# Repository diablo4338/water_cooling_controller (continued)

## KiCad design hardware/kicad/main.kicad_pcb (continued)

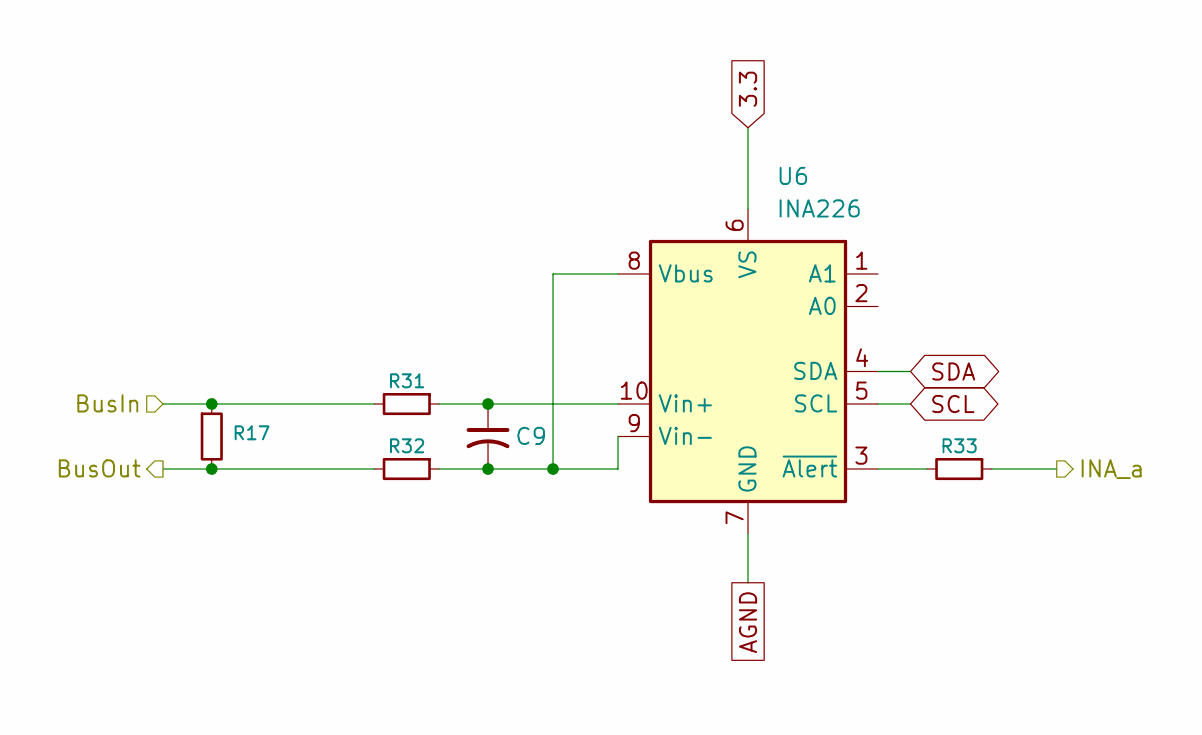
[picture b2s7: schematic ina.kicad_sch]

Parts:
C9: 0.1; C_0805_2012Metric_Pad1.18x1.45mm_HandSolder
R17: WSL2512R0470FEA; R_2512_6332Metric_Pad1.40x3.35mm_HandSolder
R31, R32: 10; R_0805_2012Metric_Pad1.20x1.40mm_HandSolder
R33: 1k; R_0805_2012Metric_Pad1.20x1.40mm_HandSolder
U6: INA226; VSSOP-10_3x3mm_P0.5mm

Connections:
3.3: U6.6 (VS); also elsewhere on the board
/esp/INA_a: R33.1; also elsewhere on the board
/fans/INA/BusIn: R17.1, R31.2; also elsewhere on the board
/fans/INA/BusOut: R17.2, R32.2; also elsewhere on the board
AGND: U6.7 (GND); also elsewhere on the board
unnamed: C9.2, R32.1, U6.8 (Vbus), U6.9 (Vin-)
unnamed: C9.1, R31.1, U6.10 (Vin+)
unnamed: R33.2, U6.3 (~Alert)
SCL: U6.5 (SCL); also elsewhere on the board
SDA: U6.4 (SDA); also elsewhere on the board

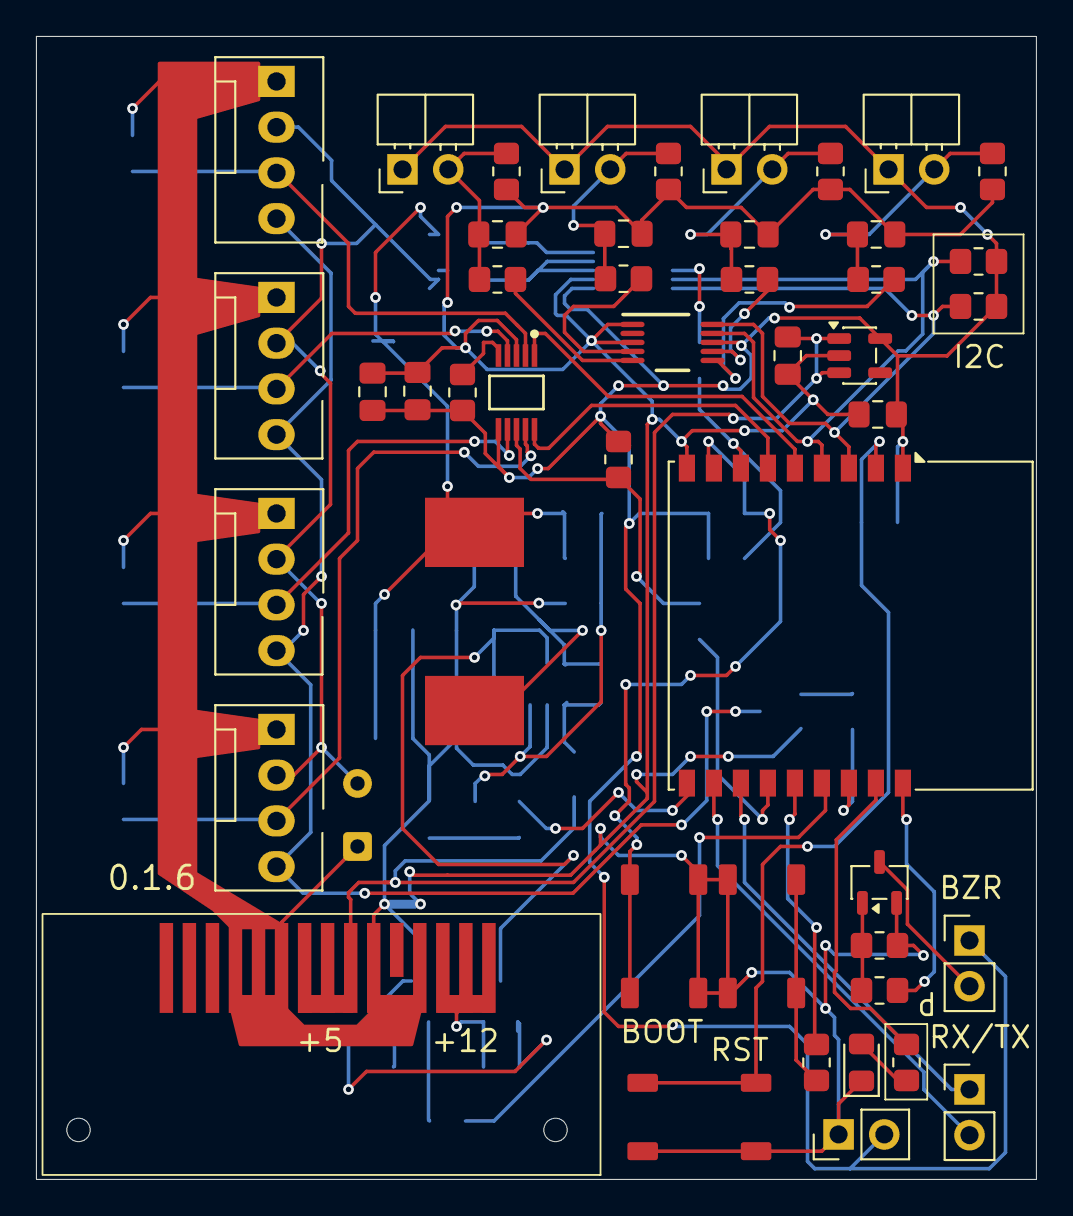
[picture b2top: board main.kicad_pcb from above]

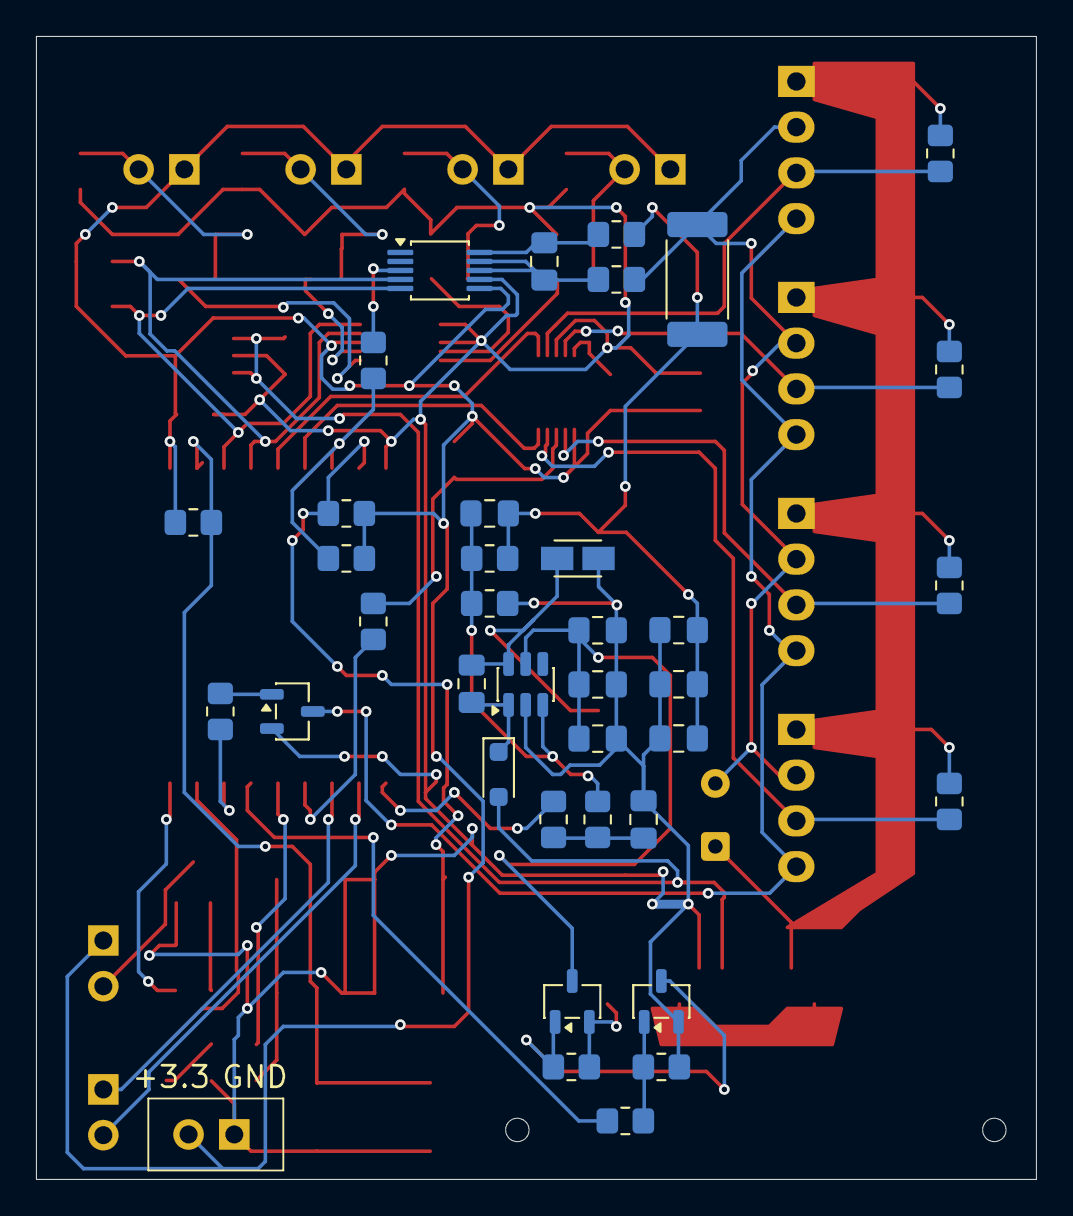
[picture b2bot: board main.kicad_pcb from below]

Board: 2 copper layers, 55.6 x 63.5 mm, 85 parts (38 on the bottom side), 53 nets.

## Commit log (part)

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2026-02-23 init
2026-02-23 Add re-pair only after reset
2026-02-23 less time to reset
2026-02-24 Move code to different files
2026-02-24 Improve pair code
2026-02-24 Improvements
2026-02-24 Improve UI
2026-02-24 Improvements, add led for debug
2026-02-24 Add retry for connect button
2026-02-24 Change debug colors
2026-02-25 Fix auth and disconnect problems
2026-02-25 Add code for simple server to test push button
2026-02-25 Add tests, refactoring
2026-02-26 Refactoring
2026-02-27 Fixes
2026-02-27 Fix log messages
2026-02-28 Fix UI
2026-02-28 Refactoring to FSM
2026-02-28 Add ads1115 adapter, remove mock service
2026-02-28 Move config to single file, handle i2c errors
2026-03-01 Add sensor threshold and init read metrics values
2026-03-01 actualize documentation
2026-03-01 change some logic inside tests
2026-03-02 fix pairing list
2026-03-02 Remove Paring action
2026-03-02 Add fan speed functional
2026-03-02 Fix tests
2026-03-12 Add params service
2026-03-12 Edit debug service
2026-03-12 Add fan control service and exceptions
2026-03-12 Add watchdog for connection
2026-03-12 Edit gitignore
2026-03-12 Add calibration operation
2026-03-12 Refactor calibration operation
2026-03-12 Refactor operation layer
2026-03-12 Refactor UI
2026-03-12 Refactor firmware code
2026-03-16 Add new parameters
2026-03-16 Make mock logic for auto-fan control
2026-03-16 Refactor operation manager
2026-03-16 Add calibration phase handling
2026-03-16 Remove unused operation
2026-03-19 Translation and complete README
2026-03-22 Fix PWM and DC
2026-04-04 Add piro firmare to test PWM
2026-04-07 Refactor pico code to raspberry
2026-04-08 Change logging strategy
2026-04-12 Change parameters, change some UI fields, finalizing fun working logic
2026-04-12 Fix fan algorithm to control
2026-04-12 UI refactoring
2026-04-12 Fix gitignore
2026-04-22 Add global FSM
2026-04-22 Add OFF mode for fan
2026-04-23 Edit calculate rpm logic
2026-04-23 Add 4 independence fans
2026-04-23 Add led indicator
2026-04-23 Refactoring device status
2026-04-24 Refactoring UI code
2026-04-24 Fix paring mode, add factory reset action
2026-04-24 Add more logs
2026-04-24 Edit timings
2026-04-25 Change UI
2026-04-25 Add overheat status
2026-04-25 Move i2c initialize procedure to independent layer
2026-04-29 Add INA226 and some UI improvements
2026-04-29 Improve INA code
2026-04-30 Improve INA code, fix overload code
2026-04-30 Add graph
2026-05-03 Add extra graph
2026-05-03 Edit UI
2026-05-03 Add default config
2026-05-03 Fix UI graph
2026-05-29 Rename saved devices
2026-05-31 UI fixes
2026-05-31 Fix metrics aggregation
2026-06-01 change rpm calculation algorithm
2026-06-01 Fix ui logs
2026-06-01 Fix shared i2c bus
2026-06-01 Fix speed calculate code
2026-06-13 Fix tests and code structure
2026-06-13 Fix structure
2026-06-13 Fix cache for release build process
2026-06-13 Reorganize file structure in project
2026-06-13 Add hardware files
2026-06-13 Edit actions files
2026-06-13 Edit production files
2026-06-13 small fixes
2026-06-14 Complete README
2026-06-15 Change deploy process, add LICENSE files
2026-06-15 Actualize production files
2026-06-15 edit actions
2026-06-19 Pack firmware to zip
2026-06-22 Change UI layout
